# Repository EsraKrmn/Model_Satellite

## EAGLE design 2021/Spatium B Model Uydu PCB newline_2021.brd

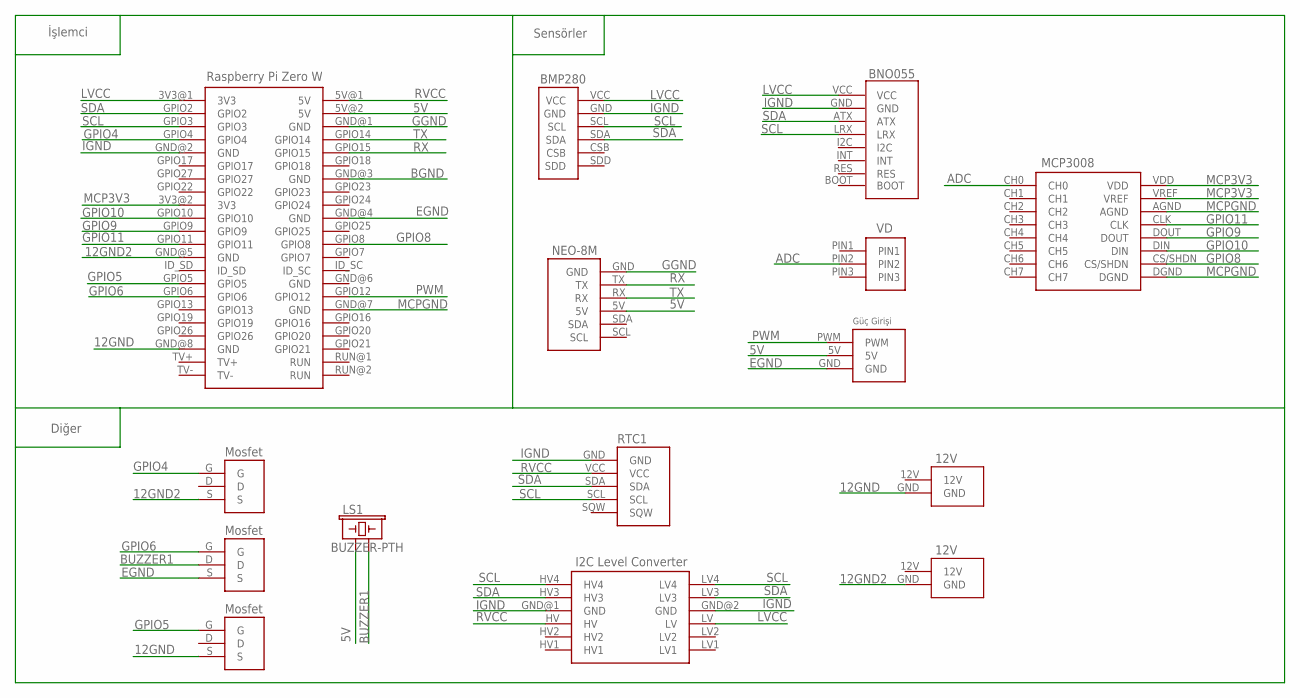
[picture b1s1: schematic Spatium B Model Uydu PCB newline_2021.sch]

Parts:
BNO1: BNO055
LS1: BUZZER-PTH; BUZZER-12MM
RTC1: PCF8523_RTC
U$1: RASPBERRY_ZERO_W
U$2: BMP280
U$3: I2C_LOGIC_LEVEL_CONVERTER
U$4: NEOM8N; NEO8M
U$5: VOLTAGE_DIVIDER
U$6, U$8, U$9: MOSFET
U$7: Güç_GIRIS
U$10, U$11: 12V
U$12: MCP3008

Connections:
5V: LS1.+ (1), U$1.5V@2 (5V), U$4.5V, U$7.5V
12GND: U$1.GND@8 (GND), U$6.S, U$10.GND
12GND2: U$1.GND@5 (GND), U$9.S, U$11.GND
ADC: U$5.PIN2, U$12.CH0
BGND: U$1.GND@3 (GND)
BUZZER1: LS1.- (2), U$8.D
EGND: U$1.GND@4 (GND), U$7.GND, U$8.S
GGND: U$1.GND@1 (GND), U$4.GND
GPIO4: U$1.GPIO4, U$9.G
GPIO5: U$1.GPIO5, U$6.G
GPIO6: U$1.GPIO6, U$8.G
GPIO8: U$1.GPIO8, U$12.CS/SHDN
GPIO9: U$1.GPIO9, U$12.DOUT
GPIO10: U$1.GPIO10, U$12.DIN
GPIO11: U$1.GPIO11, U$12.CLK
IGND: BNO1.GND, RTC1.GND, U$1.GND@2 (GND), U$2.GND, U$3.GND@1 (GND), U$3.GND@2 (GND)
LVCC: BNO1.VCC, U$1.3V3@1 (3V3), U$2.VCC, U$3.LV
MCP3V3: U$1.3V3@2 (3V3), U$12.VDD, U$12.VREF
MCPGND: U$1.GND@7 (GND), U$12.AGND, U$12.DGND
PWM: U$1.GPIO12, U$7.PWM
RVCC: RTC1.VCC, U$1.5V@1 (5V), U$3.HV
RX: U$1.GPIO15, U$4.TX
SCL: BNO1.LRX, RTC1.SCL, U$1.GPIO3, U$2.SCL, U$3.HV4, U$3.LV4
SDA: BNO1.ATX, RTC1.SDA, U$1.GPIO2, U$2.SDA, U$3.HV3, U$3.LV3
TX: U$1.GPIO14, U$4.RX

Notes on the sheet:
İşlemci
Sensörler
Diğer

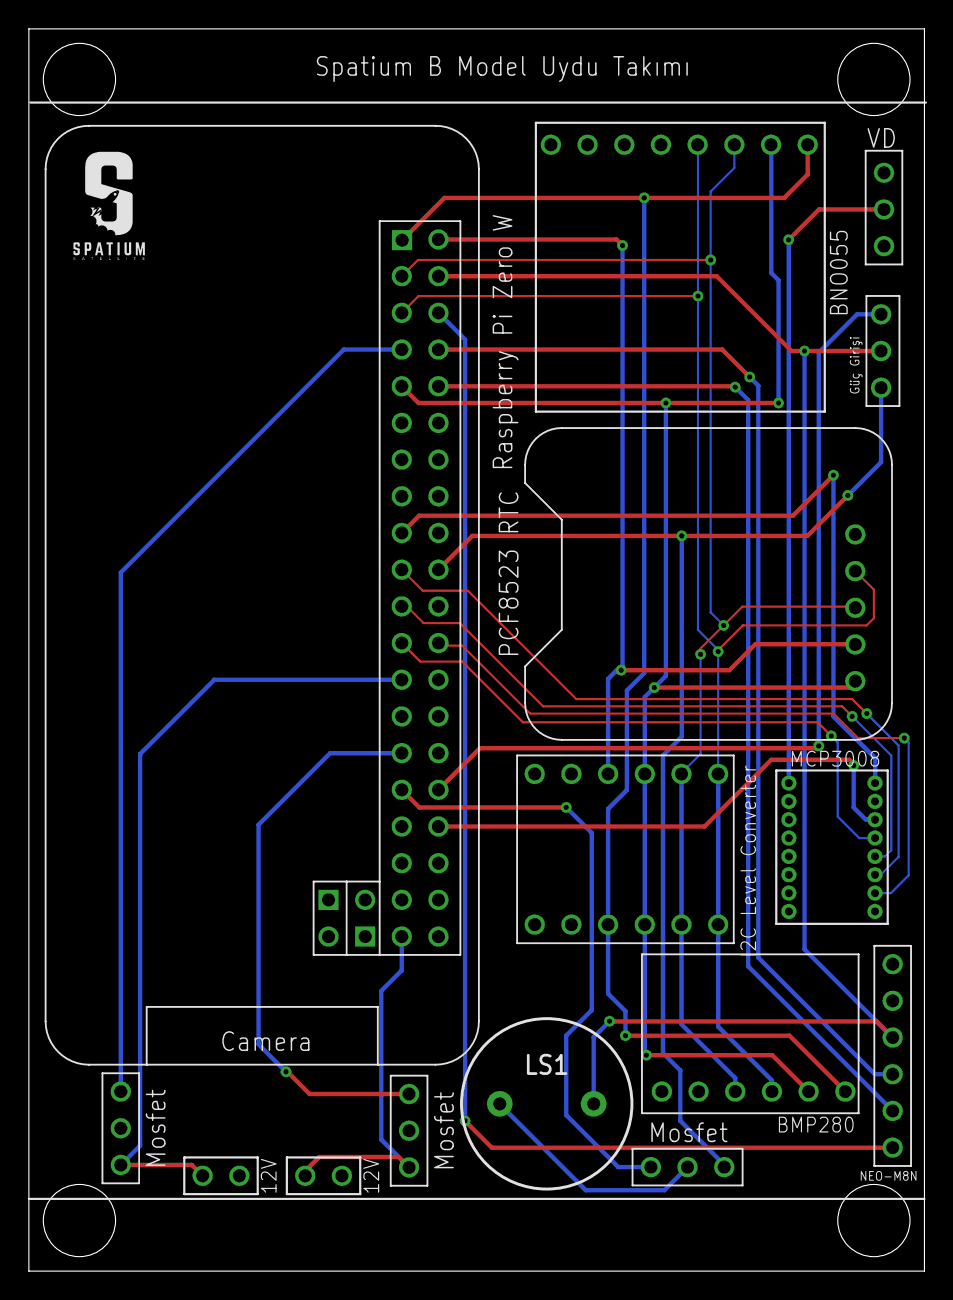
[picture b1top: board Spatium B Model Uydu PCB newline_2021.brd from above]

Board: 2 copper layers, 62.0 x 86.0 mm, 15 parts (0 on the bottom side), 24 nets.

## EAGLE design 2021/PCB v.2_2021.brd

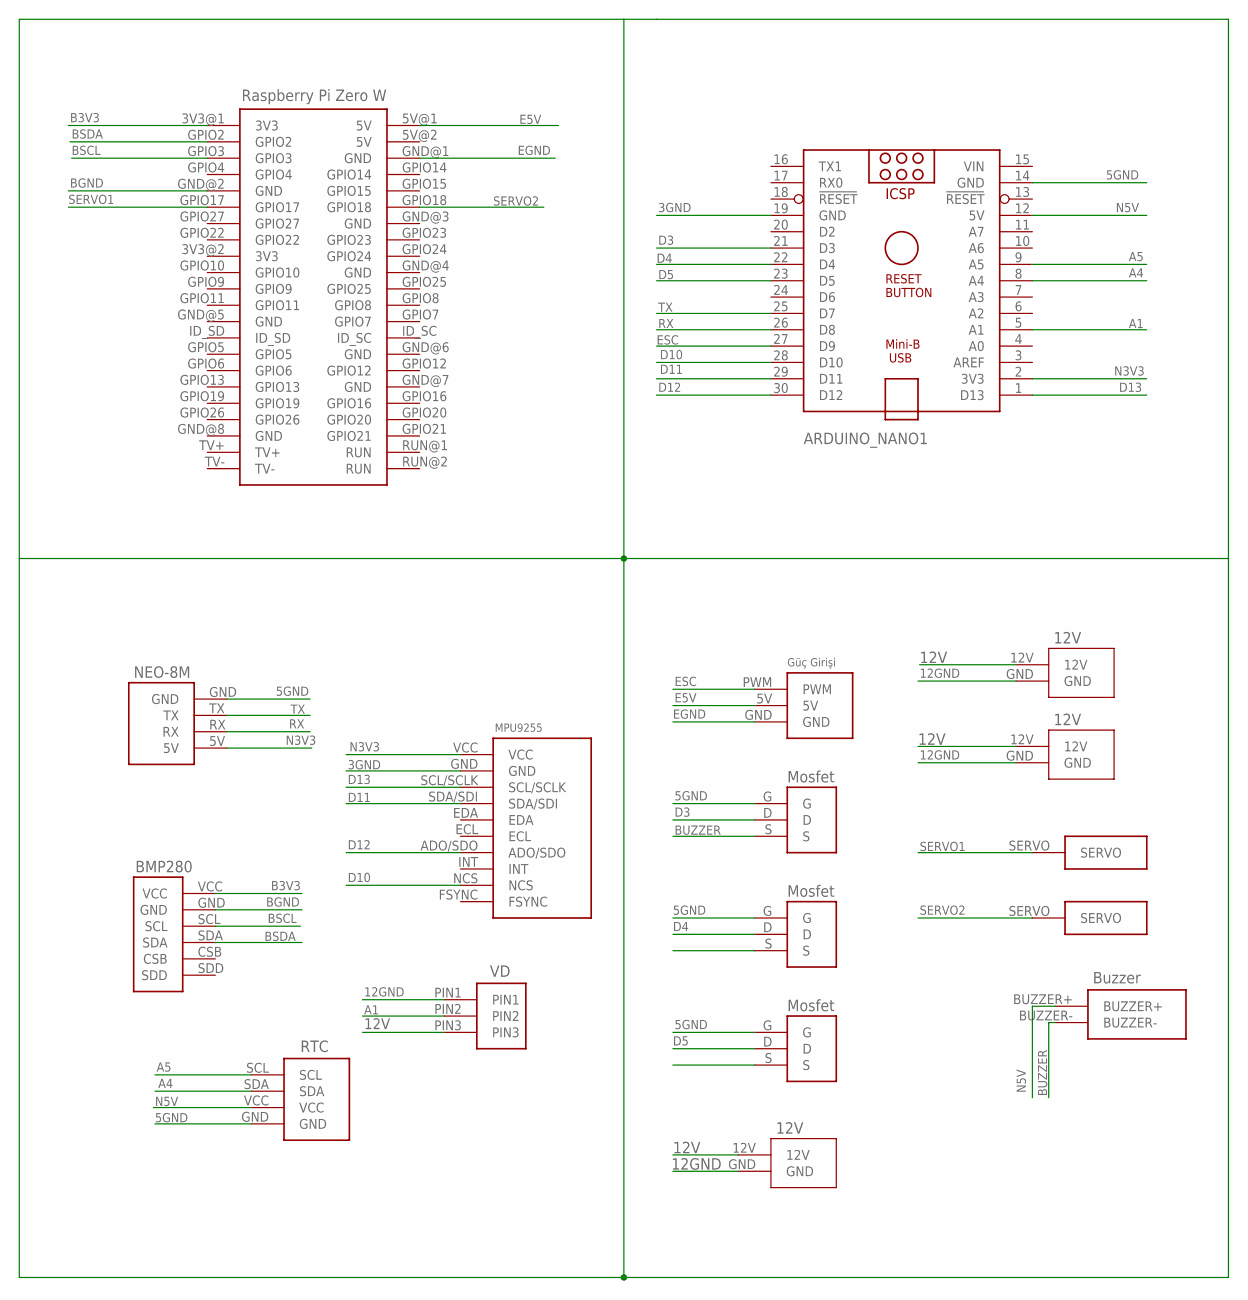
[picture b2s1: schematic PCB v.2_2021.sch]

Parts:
ARDUINO_NANO1: ARDUINO_NANO
BMP1: BMP280
RPIZEROW1: RASPBERRY_ZERO_W
U$1: NEOM8N; NEO8M
U$2: MPU9255
U$3: VOLTAGE_DIVIDER
U$4: ESC_GIRIS
U$5, U$6, U$13: 12V
U$7, U$8, U$9: MOSFET
U$10: RTC
U$11, U$12: SERVO_SIGNAL
U$14: BUZZER

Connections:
3GND: ARDUINO_NANO1.19 (GND), U$2.GND
5GND: ARDUINO_NANO1.14 (GND), U$1.GND, U$7.G, U$8.G, U$9.G, U$10.GND
12GND: U$3.PIN1, U$5.GND, U$6.GND, U$13.GND
12V: U$3.PIN3, U$5.12V, U$6.12V, U$13.12V
A1: ARDUINO_NANO1.5 (A1), U$3.PIN2
A4: ARDUINO_NANO1.8 (A4), U$10.SDA
A5: ARDUINO_NANO1.9 (A5), U$10.SCL
B3V3: BMP1.VCC, RPIZEROW1.3V3@1 (3V3)
BGND: BMP1.GND, RPIZEROW1.GND@2 (GND)
BSCL: BMP1.SCL, RPIZEROW1.GPIO3
BSDA: BMP1.SDA, RPIZEROW1.GPIO2
BUZZER: U$7.S, U$14.BUZZER-
D3: ARDUINO_NANO1.21 (D3), U$7.D
D4: ARDUINO_NANO1.22 (D4), U$8.D
D5: ARDUINO_NANO1.23 (D5), U$9.D
D10: ARDUINO_NANO1.28 (D10), U$2.NCS
D11: ARDUINO_NANO1.29 (D11), U$2.SDA/SDI
D12: ARDUINO_NANO1.30 (D12), U$2.ADO/SDO
D13: ARDUINO_NANO1.1 (D13), U$2.SCL/SCLK
E5V: RPIZEROW1.5V@1 (5V), U$4.5V
EGND: RPIZEROW1.GND@1 (GND), U$4.GND
ESC: ARDUINO_NANO1.27 (D9), U$4.PWM
N3V3: ARDUINO_NANO1.2 (3V3), U$1.5V, U$2.VCC
N5V: ARDUINO_NANO1.12 (5V), U$10.VCC, U$14.BUZZER+
RX: ARDUINO_NANO1.26 (D8), U$1.RX
SERVO1: RPIZEROW1.GPIO17, U$11.SERVO
SERVO2: RPIZEROW1.GPIO18, U$12.SERVO
TX: ARDUINO_NANO1.25 (D7), U$1.TX
VIN: ARDUINO_NANO1.15 (VIN)

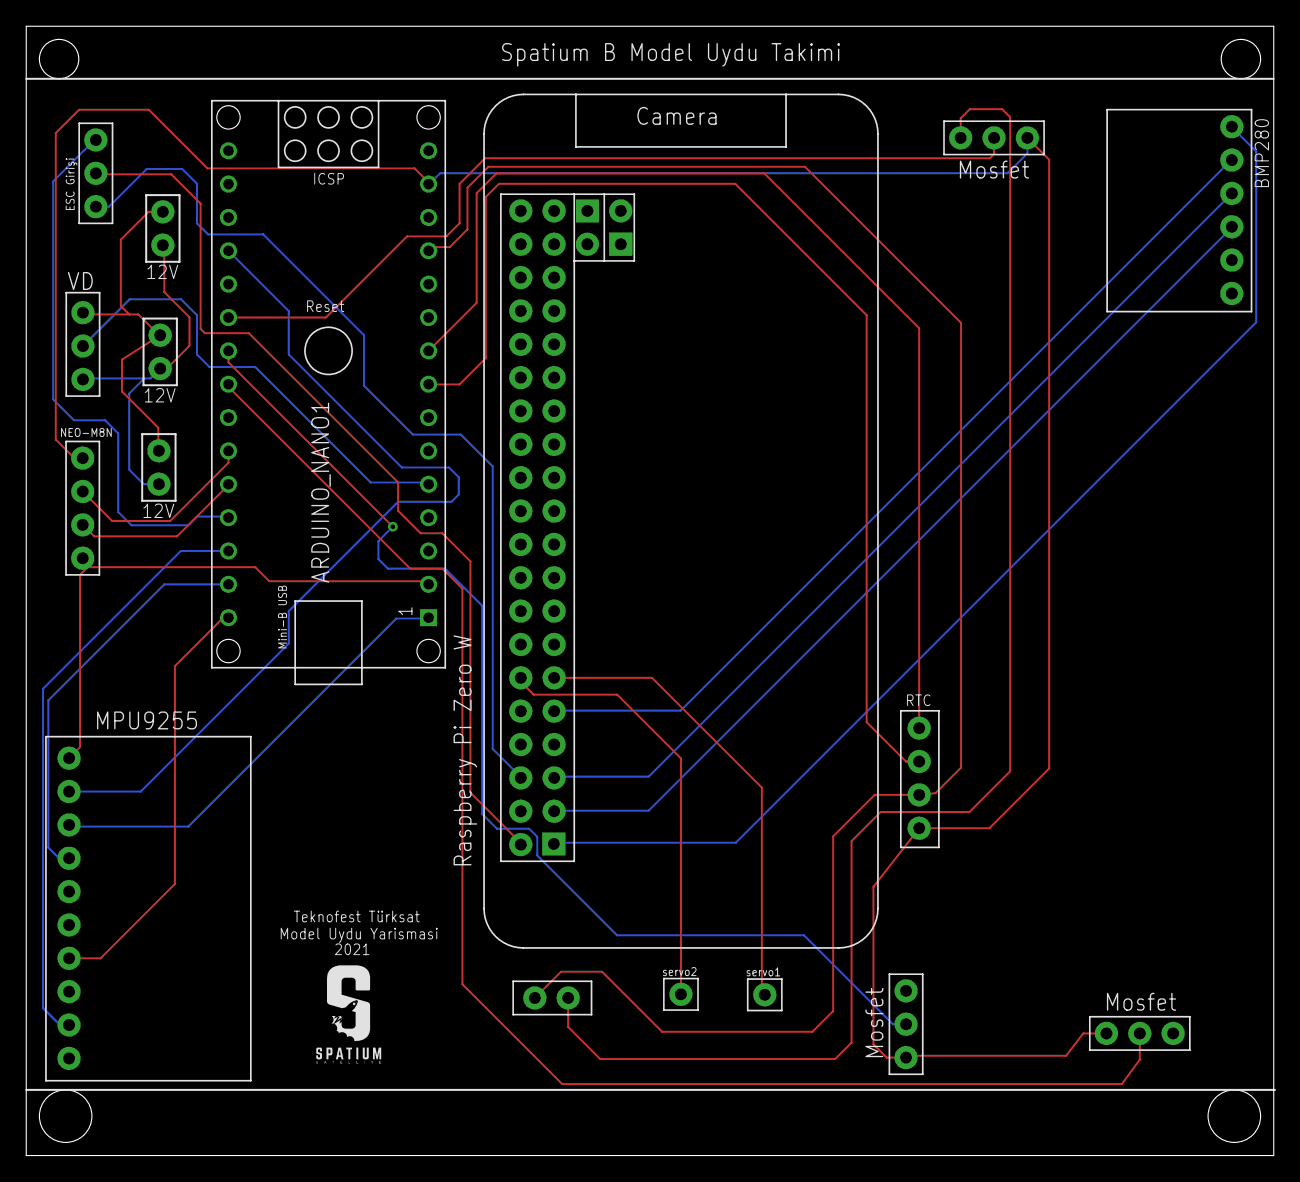
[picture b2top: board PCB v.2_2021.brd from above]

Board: 2 copper layers, 95.0 x 86.0 mm, 17 parts (0 on the bottom side), 28 nets.

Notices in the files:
parts and their libraries:
SparkFun-Electromechanical: Licensing: Creative Commons ShareAlike 4.0 International - https://creativecommons.org/licenses/by-sa/4.0
